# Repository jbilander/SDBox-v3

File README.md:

# SDBox-v3
A parallel to Pico 2 W and sd-card project for the Amiga

***

Firmware for this project with support for a blinking activity LED can be built from source here:<br />
https://github.com/jbilander/amiga-par-to-spi-adapter/tree/master/rp2350

***

***

***

***
BOM Rev. 3C
---------
same as 3B but with these changes:
Reference  | Name/Value   | Package | Notes
-|-|-|-|
BT1 | Push button | Sunrom_Tactile_Switch_3x4x2mm_SMD_2-Pin | [Aliexpress](https://www.aliexpress.com/item/4001107238344.html)
D1-D2 (Optional) | SMD LED | 0603 | [Aliexpress](https://www.aliexpress.com/item/1005003836509392.html)
R1 (Optional) | 1k Ω | 0805 | (Mandatory if D1 populated) Series resistor for D1 LED, adjust R-value to your type of LED and preferred brightness
R2 (Optional) | 1k Ω | 0805 | (Mandatory if D2 populated) Series resistor for D2 LED, adjust R-value to your type of LED and preferred brightness

***

BOM Rev. 3B
---------
Reference  | Name/Value   | Package | Notes
-|-|-|-|
U1 | Raspberry Pi Pico 2 W | SC1633 (without header) | [RPi Pico 2 W](https://www.mouser.com/ProductDetail/358-SC1633)
U2 | SN74CBT16210 | TSSOP-48 6.1x12.5mm_P0.5mm | 20-BIT FET Bus switch with level shifting, high-speed TTL-compatible. [SN74CBT16210CDGGR ](https://www.mouser.com/ProductDetail/595-SN74CBT16210CDGG)
J1 | DB25_Male | DSUB-25_Male_EdgeMount_P2.77mm| DB25 Male [Aliexpress](https://www.aliexpress.com/item/1005006354086316.html)
J2 | Sunrom Micro SD Card Holder | 9-pin Micro SD card slot connector | Sunrom Micro-SD [Aliexpress](https://www.aliexpress.com/item/32802051702.html)
J3 | (Optional) UART0 PinHeader | 5-pin 2.54 mm pitch single row | Optional 5V-tolerant header for UART0 (TX on GP12, RX on GP13) 
JP1 | (Optional) PinHeader/Jumper shunt | 2-pin 2.54 mm pitch single row | Jumper on connects Amiga /RESET signal together with RUN-pin (pin 30) on Pico 2 W, resets pico on Ctrl-A-A
D1 (Optional) | LED Square 2x5x7mm | PinHeader_1x02_P2.54mm_Vertical, pin pitch 2.54 mm | Power LED indicator [Aliexpress](https://www.aliexpress.com/item/1005006220921860.html)
D2 (Optional) | LED Square 2x5x7mm | PinHeader_1x02_P2.54mm_Vertical, pin pitch 2.54 mm | Activity LED indicator [Aliexpress](https://www.aliexpress.com/item/1005006220921860.html)
D3 | MMDL6050T1G Small Signal Switching Diode 200mA | SOD-323 | [MMDL6050T1G](https://www.mouser.com/ProductDetail/863-MMDL6050T1G)
R1 (Optional) | 4.7k Ω | 0805 | (Mandatory if D1 populated) Series resistor for D1 LED, adjust R-value to your type of LED and preferred brightness
R2 (Optional) | 220 Ω | 0805 | (Mandatory if D2 populated) Series resistor for D2 LED, adjust R-value to your type of LED and preferred brightness
R3 (Optional) | 10k Ω | 0603 | Pull-up for /STROBE signal, not currently used
R4 | 2.9k - 3k Ω | 0603 | Resistor for dummy loading D3 to achieve steady 0.6-0.7V VCC drop resulting in ~4.3V power supply to U2 [CR0603-FX-2941ELF](https://www.mouser.com/ProductDetail/652-CR0603FX-2941ELF)
RN1, RN2 | CAY16-103J4LF RES ARRAY 4 Resistors 10k Ω | 1206 | [CAY16-103J4LF](https://www.mouser.com/ProductDetail/652-CAY16-103J4LF)
RN3 | A103J | Bussed Resistor Network Array SIP-9 | Pull-up resistors for data lines, 9PIN-10K [Aliexpress](https://www.aliexpress.com/item/1005006954621214.html)
C1 | Capacitor 10uF | 1206 | 
C2 | Capacitor 0.1uF = 100nF | 0805 | 
C3 | Capacitor 0.1uF = 100nF | 0603 |
Housing | 2 x Plastic Shell Cover | For DB25 plug | [Aliexpress](https://www.aliexpress.com/item/1005004717091904.html)
2 x PinHeader | PinHeader Board Weight/Level Support | 3-pin 2.54 mm pitch single row | Move the plastic guard to leave ~7.5 mm of pin before soldering in order to hold board in perfect level

***

When ordering from JLCPCB select:

Specify Layer Sequence: Yes

    L1(Top layer):    F_Cu.gbr
    L2(Inner layer1): GND_Cu.gbr
    L3(Inner layer2): VCC_Cu.gbr
    L4(Bottom layer): B_Cu.gbr

Remove Order Number: 

    Specify a location

This will notify JLC where to put the order number, they will replace the "JLCJLCJLCJLC" silkscreen label.

***

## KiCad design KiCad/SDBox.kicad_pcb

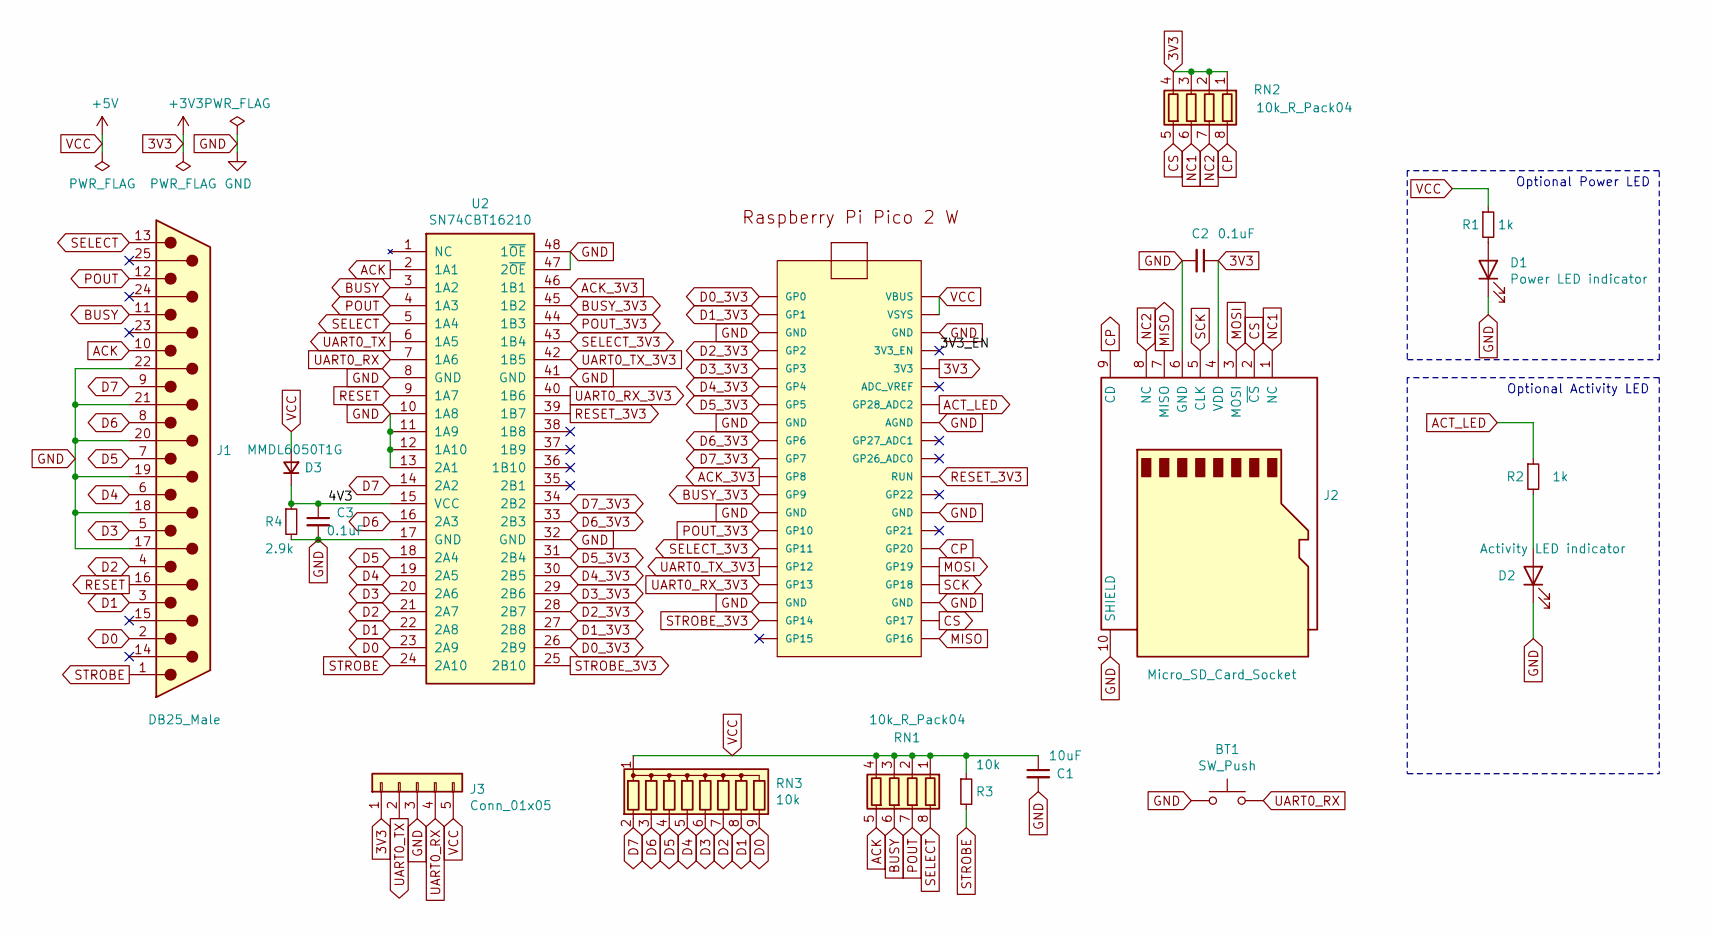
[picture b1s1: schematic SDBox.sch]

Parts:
BT1: SW_Push; Sunrom_Tactile_Switch_3x4x2mm_SMD_2-Pin
C1: 10uF; C_1206_3216Metric_Pad1.33x1.80mm_HandSolder
C2: 0.1uF; C_0805_2012Metric_Pad1.15x1.40mm_HandSolder
C3: 0.1uF; C_0603_1608Metric_Pad1.08x0.95mm_HandSolder
D1: Power LED indicator; D_0603_1608Metric_Pad1.05x0.95mm_HandSolder
D2: Activity LED indicator; D_0603_1608Metric_Pad1.05x0.95mm_HandSolder
D3: MMDL6050T1G; D_0603_1608Metric_Pad1.05x0.95mm_HandSolder
J1: DB25_Male; DSUB-25_Male_EdgeMount_P2.77mm
J2: Micro_SD_Card_Socket; GCT-MEM2055-00-190-01-A
J3: Conn_01x05; UART_PinHeader_SMD_pads_2.54mm_pitch
R1, R2: 1k; R_0805_2012Metric_Pad1.15x1.40mm_HandSolder
R3: 10k; R_0603_1608Metric_Pad0.98x0.95mm_HandSolder
R4: 2.9k; R_0603_1608Metric_Pad0.98x0.95mm_HandSolder
RN1, RN2: 10k_R_Pack04; RESCAF80P320X160X60-8N
RN3: 10k; R_Array_SIP9
U1: Rapberry_Pi_Pico_2W; RPi_Pico_SMD
U2: SN74CBT16210; TSSOP-48_6.1x12.5mm_P0.5mm

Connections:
3V3: C2.1, J2.4 (VDD), J3.1, RN2.1 (R1.1), RN2.2 (R2.1), RN2.3 (R3.1), RN2.4 (R4.1), U1.36 (3V3)
/3V3_EN: U1.37 (3V3_EN)
/4V3: C3.1, D3.1 (K), R4.1, U2.15 (VCC)
ACK: J1.10, RN1.5 (R4.2), U2.2 (1A1)
ACK_3V3: U1.11 (GP8), U2.46 (1B1)
ACT_LED: R2.1, U1.34 (GP28_ADC2)
BUSY: J1.11, RN1.6 (R3.2), U2.3 (1A2)
BUSY_3V3: U1.12 (GP9), U2.45 (1B2)
CP: J2.9 (CD), RN2.8 (R1.2), U1.26 (GP20)
CS: J2.2 (~CS), RN2.5 (R4.2), U1.22 (GP17)
D0: J1.2, RN3.9 (R8), U2.23 (2A9)
D0_3V3: U1.1 (GP0), U2.26 (2B9)
D1: J1.3, RN3.8 (R7), U2.22 (2A8)
D1_3V3: U1.2 (GP1), U2.27 (2B8)
D2: J1.4, RN3.7 (R6), U2.21 (2A7)
D2_3V3: U1.4 (GP2), U2.28 (2B7)
D3: J1.5, RN3.6 (R5), U2.20 (2A6)
D3_3V3: U1.5 (GP3), U2.29 (2B6)
D4: J1.6, RN3.5 (R4), U2.19 (2A5)
D4_3V3: U1.6 (GP4), U2.30 (2B5)
D5: J1.7, RN3.4 (R3), U2.18 (2A4)
D5_3V3: U1.7 (GP5), U2.31 (2B4)
D6: J1.8, RN3.3 (R2), U2.16 (2A3)
D6_3V3: U1.9 (GP6), U2.33 (2B3)
D7: J1.9, RN3.2 (R1), U2.14 (2A2)
D7_3V3: U1.10 (GP7), U2.34 (2B2)
GND: BT1.1, C1.2, C2.2, C3.2, D1.1 (K), D2.1 (K), J1.17, J1.18, J1.19, J1.20, J1.21, J1.22, J2.6 (GND), J2.10 (SHIELD), J3.3, R4.2, U1.3 (GND), U1.8 (GND), U1.13 (GND), U1.18 (GND), U1.23 (GND), U1.28 (GND), U1.33 (AGND), U1.38 (GND), U2.8 (GND), U2.10 (1A8), U2.11 (1A9), U2.12 (1A10), U2.13 (2A1), U2.17 (GND), U2.32 (GND), U2.41 (GND), U2.47 (2~OE), U2.48 (1~OE)
MISO: J2.7 (MISO), U1.21 (GP16)
MOSI: J2.3 (MOSI), U1.25 (GP19)
NC1: J2.1 (NC), RN2.6 (R3.2)
NC2: J2.8 (NC), RN2.7 (R2.2)
unnamed: D1.2 (A), R1.2
unnamed: D2.2 (A), R2.2
POUT: J1.12, RN1.7 (R2.2), U2.4 (1A3)
POUT_3V3: U1.14 (GP10), U2.44 (1B3)
RESET: J1.16, U2.9 (1A7)
RESET_3V3: U1.30 (RUN), U2.39 (1B7)
SCK: J2.5 (CLK), U1.24 (GP18)
SELECT: J1.13, RN1.8 (R1.2), U2.5 (1A4)
SELECT_3V3: U1.15 (GP11), U2.43 (1B4)
STROBE: J1.1, R3.2, U2.24 (2A10)
STROBE_3V3: U1.19 (GP14), U2.25 (2B10)
UART0_RX: BT1.2, J3.4, U2.7 (1A6)
UART0_RX_3V3: U1.17 (GP13), U2.40 (1B6)
UART0_TX: J3.2, U2.6 (1A5)
UART0_TX_3V3: U1.16 (GP12), U2.42 (1B5)
VCC: C1.1, D3.2 (A), J3.5, R1.1, R3.1, RN1.1 (R1.1), RN1.2 (R2.1), RN1.3 (R3.1), RN1.4 (R4.1), RN3.1 (common), U1.39 (VSYS), U1.40 (VBUS)

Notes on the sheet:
Optional Activity LED
Optional Power LED

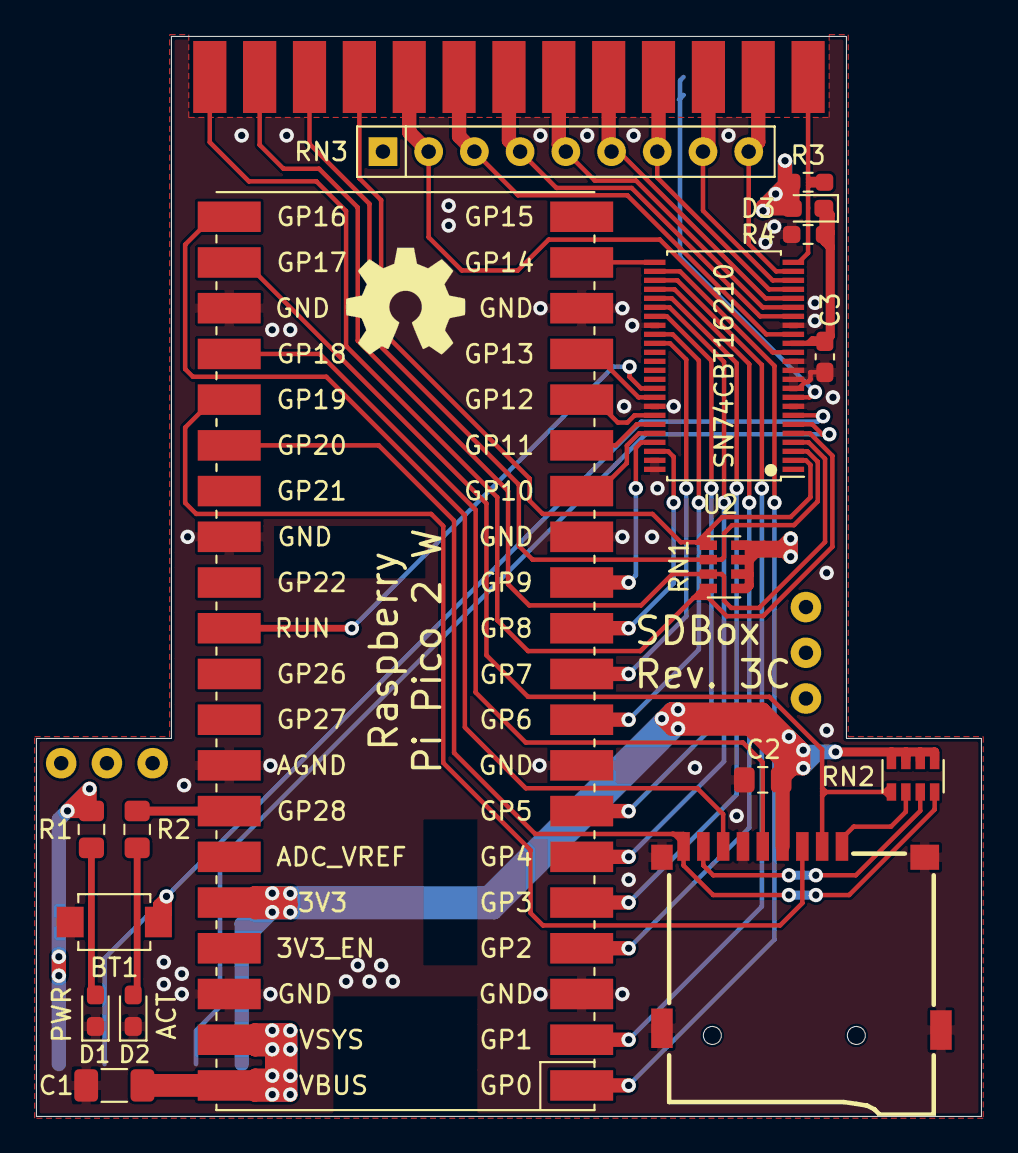
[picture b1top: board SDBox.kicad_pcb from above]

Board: 4 copper layers, 52.5 x 60.0 mm, 19 parts (1 on the bottom side), 46 nets.

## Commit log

2025-05-12 Add footprint
2025-05-12 Add 3D-model
2025-05-12 Add KiCad files
2025-05-14 Add Rapberry_Pi_Pico_2W symbol
2025-05-14 Add Rapberry_Pi_Pico_2W and +5V flag for VCC
2025-05-14 Update board with latest setup
2025-05-14 Update design to accomodate a Rapberry_Pi_Pico_2W
2025-05-14 Place and route R3
2025-05-15 Add RN3 (pull-ups for data lines), fixed keep-out areas for header and test-points on RPi Pico 2 W
2025-05-15 Change board to four layer
2025-05-15 Add track width 0.3 mm
2025-05-15 Add SN74CBT16210 symbol
2025-05-15 Change U2 SN74CB3T16210 to SN74CBT16210 and add diode D3 and resistor R4 to drop VCC to 4.3V power supply for U2
2025-05-15 Change Micro_SD_Card_Socket drill holes to 1 mm
2025-05-15 Add UART0_TX and UART0_RX through level shifter
2025-05-15 Improve ground stitching
2025-05-15 Add UART pinheader on underside with TX0 (GP12), RX0 (GP13) and Power and GND
2025-05-16 Improve routing
2025-05-16 silkscreen fixes
2025-05-16 Change to correct path (packages3d folder) for SD card slot 3D-model
2025-05-17 Small fix improved positioning of a GND via and the UART0_RX via
2025-05-19 Change R1,R2 value from 220 to 330 Ohm, change D3 value from D_small to MMDL6050T1G
2025-05-30 Add two PinHeader_1x03_P2.54mm for support structure, fix of edge cuts for better fit plastic shells
2025-05-31 Update plot params
2025-06-23 Add images
2025-06-26 Extended board 1 mm, moved RN3 0.5 mm on Y-axis and changed hole size on JP1, D1, D2 to 0.8 mm, bumped revision to 3B
2025-06-26 Change R1 value from 330 to 4.7k, Change R2 value from 330 to 220
2025-06-26 Add schematic pdf
2025-07-12 Small fix moving two GND vias to align with the rest (cosmetic fix)
2025-12-31 Add push button to GPIO13, remove JP1 and connect /RESET directly to RUN, change to 0603 SMD LED diodes, change resistor values on R1,R2 to 1k Ohm, move J3 to not interfere with USB-cable, bump revis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
2026-02-10 Update images to rev 3c
